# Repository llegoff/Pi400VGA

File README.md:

[:fr:](LISEZMOI.md) [:uk:](README.md)

# Pi400VGA
VGA interface for Raspberry Pi 400

:warning: for retrogaming on CRT see Scart/VGA interface : https://github.com/llegoff/Pi400RGB

for pi zero see https://github.com/llegoff/VGA_Zero

buy on [ebay](https://www.ebay.fr/itm/154872763613) :package:  

### DPI (Display parallel Interface)
Like [VGA666](https://github.com/fenlogic/vga666), this pcb uses dpi interface (in mode 3 to free gpio 18 & 19)

see https://www.raspberrypi.org/documentation/hardware/raspberrypi/dpi/README.md

only the necessary bits of the dpi are redirected to the 40-pin GPIO port, with the 'gpio=2-8,12-17,20-24=a2' line on config.txt

/boot/config.txt
    
    # disable i2c, pin use by h-sync & v-sync
    dtparam=i2c_arm=off
    # replace dtoverlay=vc4-kms-v3d with
    dtoverlay=vc4-fkms-v3d
    #DPI config
    gpio=2-8,12-17,20-24=a2
    dpi_output_format=0x13
    enable_dpi_lcd=1
    display_default_lcd=1
    dpi_group=2
    dpi_mode=16
    #---------------- dpi_mode line ---------------------
    #---> 640x480 60hz    dpi_mode=4
    #---> 800x600 60hz    dpi_mode=9
    #---> 1024x768 60hz   dpi_mode=16
    #---> 1280x768 60hz   dpi_mode=23
    #---> 1280x800 60hz   dpi_mode=28
    #---> 1280x960 60hz   dpi_mode=32
    #---> 1280x1024 60hz  dpi_mode=35
    #---> 1360x768 60hz   dpi_mode=39
    #---> 1366x768 60hz   dpi_mode=81
    #---> 1400x1050 60hz  dpi_mode=42
    #---> 1440x900 60hz   dpi_mode=47
    #---> 1600x1200 60hz  dpi_mode=51
    #---> 1680x1050 60hz  dpi_mode=58
    #---> 1920x1080 60hz  dpi_mode=82
    #---> 1920x1200 60hz  dpi_mode=69
    #---> 1920x1440 60hz  dpi_mode=73

Configuration working with vc4-kms-v3d

    dtoverlay=vc4-kms-dpi-generic,rgb565-padhi
    dtparam=hactive=800,hfp=40,hsync=128,hbp=88
    dtparam=vactive=600,vfp=1,vsync=4,vbp=23
    dtparam=clock-frequency=40000000
    #   Resolution@freq  hactive hfp hsync  hbp vactive vfp vsync vbp  clock-frequency
    #VGA   640x480  @60   640     16   96    48   480    10   2    33    25175000
    #SVGA  800x600  @60   800     40  128    88   600     1   4    23    40000000
    #XGA  1024x768  @60  1024     24  136   160   768     3   6    29    65000000
    #VESA 1368x768  @60  1368     72  144   216   768     1   3    23    85860000
    #VESA 1280x800  @60  1280     64  136   200   800     1   3    24    83460000
    #VESA 1280x1024 @60  1280     48  112   248  1024     1   3    38   108000000
    #VESA 1400x1050 @60  1400     88  152   240  1050     1   3    33   122660000
    #VESA 1600x1200 @60  1600     64  192   304  1200     1   3    46   162000000
    #--- TV -----
    #244p (NTSC res)@60   320      4   30    46   240     4   5    14     6400000
    #288p (PAL res) @50   384     16   32    40   288     3   2    19     7363200
    #480i (NTSC res)@60   640     24   64   104   480     3   6    34    13054080
    #576i (PAL res) @50   768     24   72    88   576     6   5    38    14875000
    #480p           @60   640     24   96    48   480    11   2    32    25452000
    #720p           @60  1280    110   40   220   720     5   5    20    74250000
    #1080p          @60  1920     88   44   148  1080     4   5    36   148500000
    #more timming on http://tinyvga.com/vga-timing

### 15khz cathode ray screen

:point_up: this config work only with Raspberry pi OS, not with Recalbox OS or RGB-Pi OS (use rpi-dpidac, who only work with dpi mode 5 & 6)

for RecalboxOS or RGB-Pi OG , see https://github.com/llegoff/Pi400RGB

    # replace dtoverlay=vc4-kms-v3d with
    dtoverlay=vc4-fkms-v3d
    # disable i2c, pin use by h-sync & v-sync
    dtparam=i2c_arm=off
    gpio=2-8,12-17,20-24=a2
    dpi_output_format=0x13
    enable_dpi_lcd=1
    display_default_lcd=1
    dpi_group=2
    dpi_mode=87
    #hdmi_timings=506 1 8 48 56 240 1 3 10 6 0 0 0 60 0 9600000 1
    #hdmi_timings=512 1 16 48 64 288 1 3 5 6 0 0 0 50 0 9600000 1
    # Custom 15kHz mode
    hdmi_timings=506 1 8 44 52 240 1 6 10 6 0 0 0 60 0 9600000 1
    #hdmi_timings=320 1 17 33 34 224 1 14 8 18 0 0 0 60 0 6400000 1
    #hdmi_timings=960 0 173 8 0 160 0 40 10 0 0 0 0 60 0 19200000 8
    #hdmi_timings=320 1 25 30 30 240 1 9 3 10 0 0 0 60 0 6400000 1
    #hdmi_timings=1920 1 52 208 260 240 1 6 10 6 0 0 0 60 0 38400000 1

### Recalbox

edit /boot/config.txt

find section 

    [pi4]
    temp_soft_limit=70
    dtoverlay=vc4-kms-v3d
    
remplace with

    [pi4]
    temp_soft_limit=70
    dtoverlay=vc4-fkms-v3d

copy content of [config-example.txt](img/config-example.txt?raw=true) to /boot/recalbox-user-config.txt
    
For crt mode , Recalbox 8 use driver rpi-dpidac, not compatible with dpi mode 3

see https://wiki.recalbox.com/en/tutorials/video/crt/crt-screen-dpi-vga666-piscart-rgbpi

### Dual Screen (VGA + HDMI)

on the pi4 and pi400, the dual screen function is supported by the vc4 fkms v3d driver

    [pi4]
    # Enable DRM VC4 V3D driver on top of the dispmanx display stack
    dtoverlay=vc4-fkms-v3d
    max_framebuffers=2

### Remote Desktop MultiMonitor
install freeRDP

    sudo apt-get install freerdp2-x11

start freeRDP session
    
    xfreerdp /v:<computer name or IP> /u:<user> /d:<domain> /sound:sys:alsa /multimon

or

    xfreerdp /v:<computer name or IP> /u:<user> /d:<domain> /g:<gateway name or IP> /gu:<gateway user> /gd:<gateway domain> /sound:sys:alsa /multimon

### Audio Interface
audio interface is connected to gpio 18 & 19 (PWM)

/boot/config.txt

    # Enable audio for PiZero(loads snd_bcm2835)
    dtoverlay=audremap,pins_18_19
    dtparam=audio=on

## Schematic

## PCB

## Installation
copy content of [config-example.txt](img/config-example.txt?raw=true) to /boot/config.txt

## Révision
rev1

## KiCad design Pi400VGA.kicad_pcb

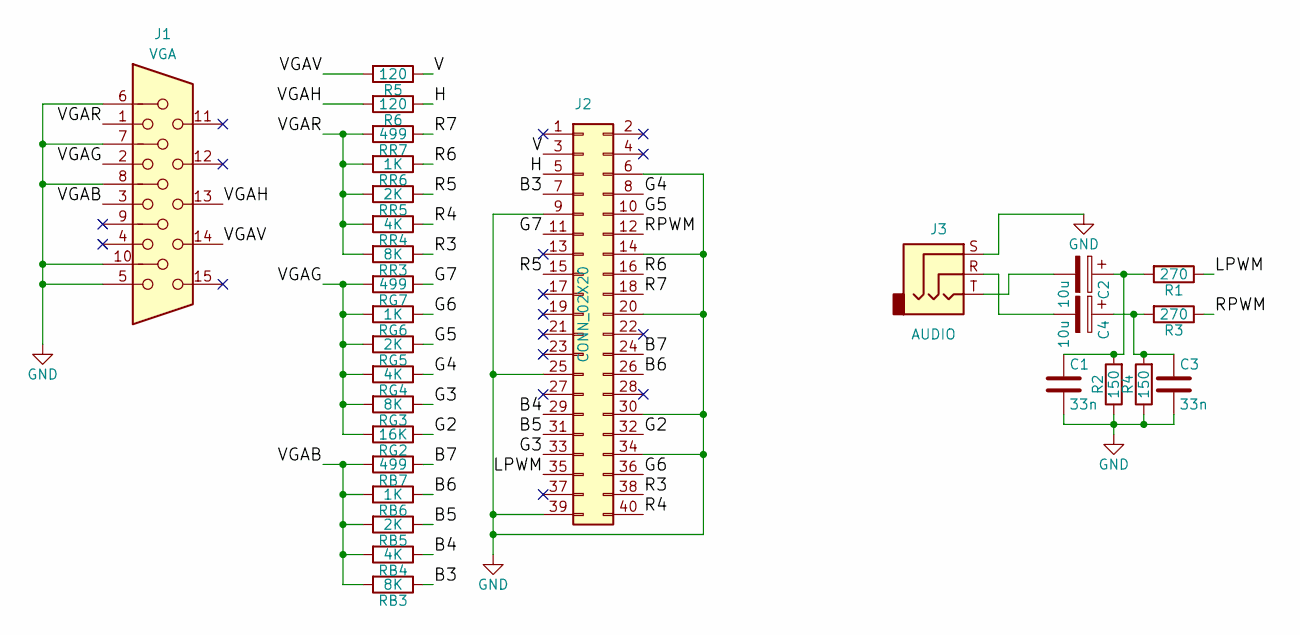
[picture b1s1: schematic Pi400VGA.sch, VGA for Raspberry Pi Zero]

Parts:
C1, C3: 33n; C_0805
C2, C4: 10u; C_0805
J1: VGA; DB_15F-VGA
J2: CONN_02X20; Socket_Strip_Straight_2x20_Pitch2.54mm
J3: AUDIO; jack3.5smd
R1, R3: 270; R_0805
R2, R4: 150; R_0805
R5, R6: 120; R_0805
RB3: 8K; R_0805
RB4: 4K; R_0805
RB5: 2K; R_0805
RB6: 1K; R_0805
RB7: 499; R_0805
RG2: 16K; R_0805
RG3: 8K; R_0805
RG4: 4K; R_0805
RG5: 2K; R_0805
RG6: 1K; R_0805
RG7: 499; R_0805
RR3: 8K; R_0805
RR4: 4K; R_0805
RR5: 2K; R_0805
RR6: 1K; R_0805
RR7: 499; R_0805

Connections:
/B3: J2.7, RB3.1
/B4: J2.29, RB4.1
/B5: J2.31, RB5.1
/B6: J2.26, RB6.1
/B7: J2.24, RB7.1
/G2: J2.32, RG2.1
/G3: J2.33, RG3.1
/G4: J2.8, RG4.1
/G5: J2.10, RG5.1
/G6: J2.36, RG6.1
/G7: J2.11, RG7.1
/H: J2.5, R6.1
/LPWM: J2.35, R1.1
/R3: J2.38, RR3.1
/R4: J2.40, RR4.1
/R5: J2.15, RR5.1
/R6: J2.16, RR6.1
/R7: J2.18, RR7.1
/RPWM: J2.12, R3.1
/V: J2.3, R5.1
/VGAB: J1.3, RB3.2, RB4.2, RB5.2, RB6.2, RB7.2
/VGAG: J1.2, RG2.2, RG3.2, RG4.2, RG5.2, RG6.2, RG7.2
/VGAH: J1.13, R6.2
/VGAR: J1.1, RR3.2, RR4.2, RR5.2, RR6.2, RR7.2
/VGAV: J1.14, R5.2
GND: C1.2, C3.2, J1.5, J1.6, J1.7, J1.8, J1.10, J2.6, J2.9, J2.14, J2.20, J2.25, J2.30, J2.34, J2.39, J3.S, R2.1, R4.1
unnamed: C1.1, C2.1, R1.2, R2.2
unnamed: C2.2, J3.T
unnamed: C3.1, C4.1, R3.2, R4.2
unnamed: C4.2, J3.R

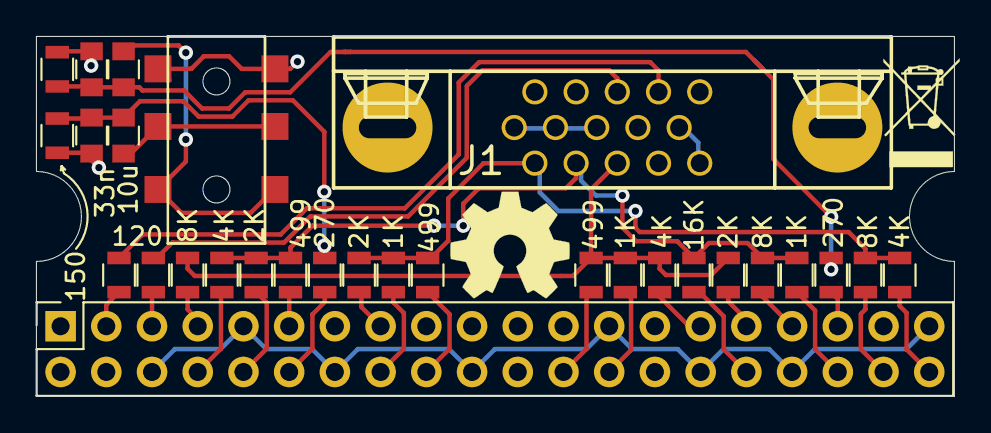
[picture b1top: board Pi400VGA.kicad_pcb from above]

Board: 2 copper layers, 51.0 x 20.0 mm, 29 parts (0 on the bottom side), 30 nets.
